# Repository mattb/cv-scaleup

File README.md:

# Control voltage step-up module

DC-coupled audio interfaces, such as the [MOTU 828 MkI](http://www.soundonsound.com/sos/jul01/articles/motu828.asp)
that I own, are capable
of [outputting voltages](http://www.expert-sleepers.co.uk/siwacompatibility.html) that can
control audio hardware such as
[Eurorack](http://electronicmusic.wikia.com/wiki/Eurorack) modules. However,
most Eurorack modules expect a CV range of -5v to 5v. I measured the MOTU as
outputting -2.88v to 2.88v.

This project contains Eagle files for a Eurorack-mountable opamp circuit with a gain that will
scale four MOTU outputs to the full CV range. It uses a single TL074 quad
op-amp and a few resistors. Calculations for the resistors were made using the calculator at 
http://earmark.net/gesr/opamp/gain_offset.htm

There is also a rudimentary 8HP front panel design in an Illustrator template.

On October 13th 2015, PCBs were ordered from OSHPark and panels from
Ponoko.  A single channel has been successfully tested on a
breadboard, and used to correctly track over 8 octaves of pitch control on
an Arturia Microbrute using Silent Way's Voice Controller plugin in Ableton Live.

On October 27th 2015, the PCBs arrived and the first one was assembled. All four channels worked correctly.

![Assembled board]
(assembled-board.jpg)

![Assembled panel]
(panel-assembled.jpg)

![Completed product in rack]
(panel-in-rack.jpg)

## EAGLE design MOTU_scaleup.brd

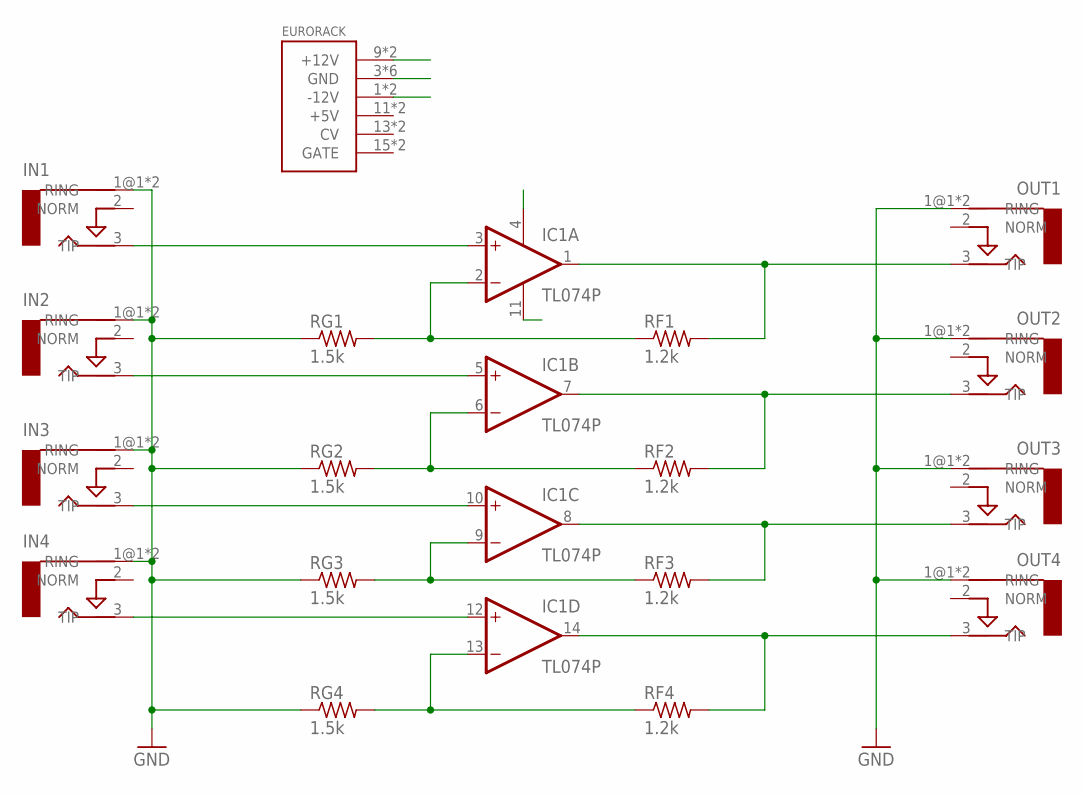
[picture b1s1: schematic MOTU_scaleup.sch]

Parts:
EURORACK: POWER; POWER_16
IC1: TL074P; DIL14
IN1, IN2, IN3, IN4: AUDIO-JACKERTHENVAR; ERTHENVAR-JACK
OUT1, OUT2, OUT3, OUT4: AUDIO-JACKERTHENVAR; ERTHENVAR-JACK
RF1, RF2, RF3, RF4: 1.2k; 0207/10
RG1, RG2, RG3, RG4: 1.5k; 0207/10

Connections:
+12V: EURORACK.9 (+12V), EURORACK.10 (+12V), IC1.4 (V+)
-12V: EURORACK.1 (-12V), EURORACK.2 (-12V), IC1.11 (V-)
GND: EURORACK.3 (GND), EURORACK.4 (GND), EURORACK.5 (GND), EURORACK.6 (GND), EURORACK.7 (GND), EURORACK.8 (GND), IN1.1@1 (RING), IN1.1@2 (RING), IN2.1@1 (RING), IN2.1@2 (RING), IN3.1@1 (RING), IN3.1@2 (RING), IN4.1@1 (RING), IN4.1@2 (RING), OUT1.1@1 (RING), OUT1.1@2 (RING), OUT2.1@1 (RING), OUT2.1@2 (RING), OUT3.1@1 (RING), OUT3.1@2 (RING), OUT4.1@1 (RING), OUT4.1@2 (RING), RG1.1, RG2.1, RG3.1, RG4.1
unnamed: IC1.3 (+IN), IN1.3 (TIP)
unnamed: IC1.5 (+IN), IN2.3 (TIP)
unnamed: IC1.10 (+IN), IN3.3 (TIP)
unnamed: IC1.12 (+IN), IN4.3 (TIP)
unnamed: IC1.14 (OUT), OUT4.3 (TIP), RF4.2
unnamed: IC1.8 (OUT), OUT3.3 (TIP), RF3.2
unnamed: IC1.7 (OUT), OUT2.3 (TIP), RF2.2
unnamed: IC1.1 (OUT), OUT1.3 (TIP), RF1.2
unnamed: IC1.6 (-IN), RF2.1, RG2.2
unnamed: IC1.9 (-IN), RF3.1, RG3.2
unnamed: IC1.13 (-IN), RF4.1, RG4.2
NNN: IC1.2 (-IN), RF1.1, RG1.2

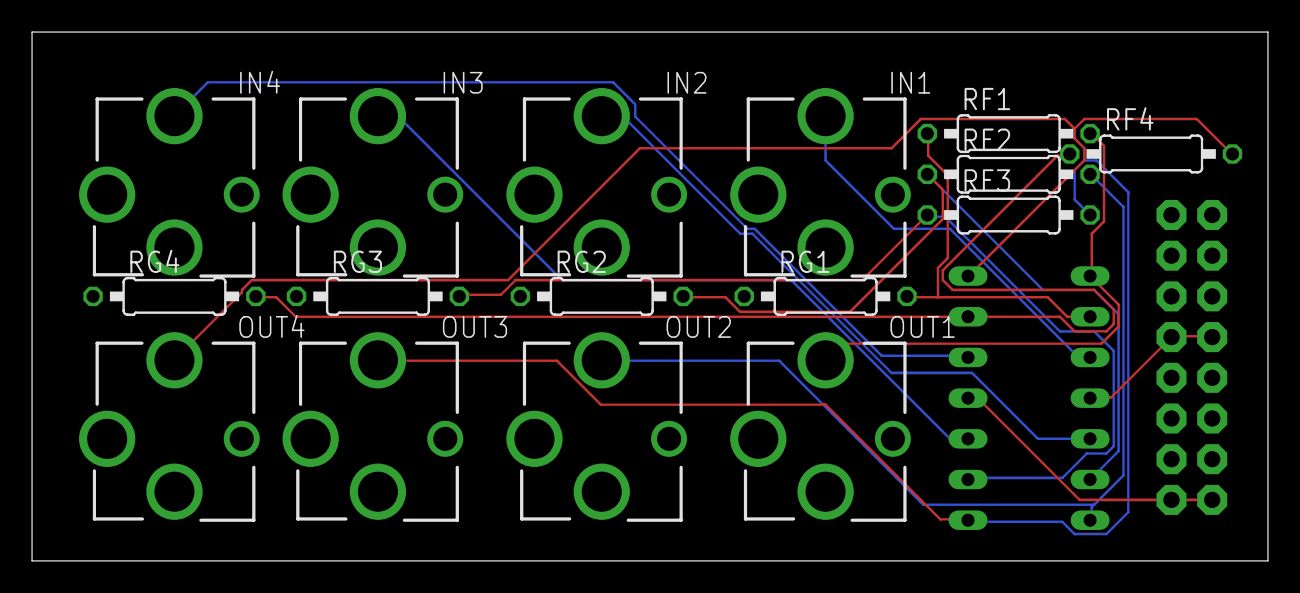
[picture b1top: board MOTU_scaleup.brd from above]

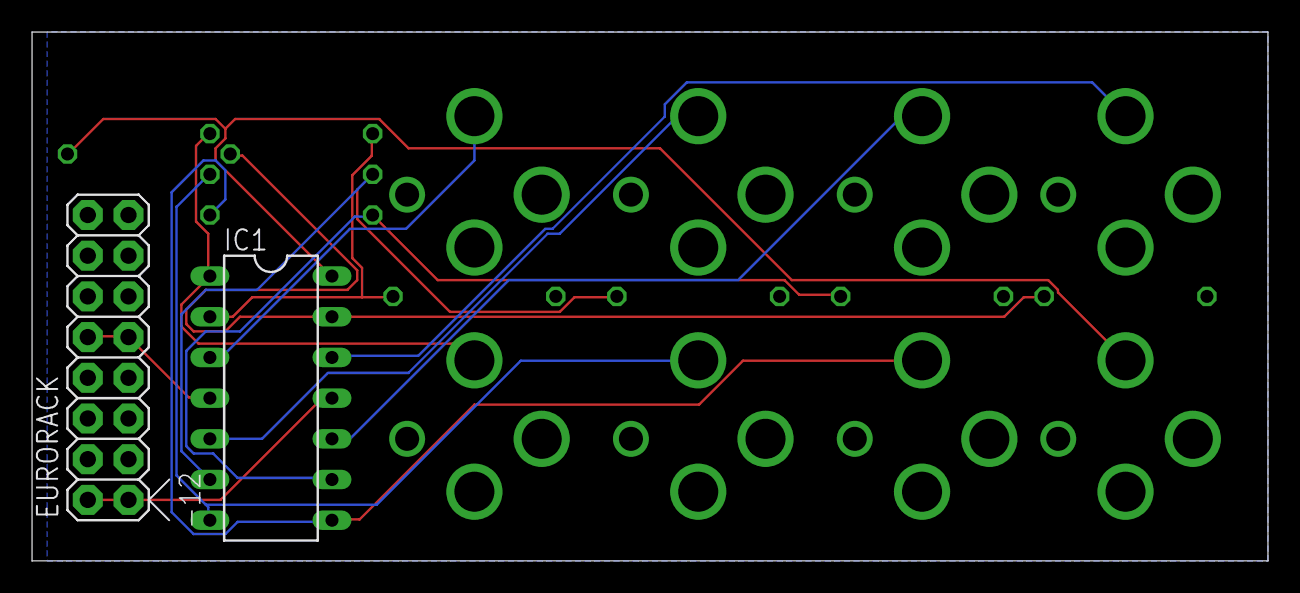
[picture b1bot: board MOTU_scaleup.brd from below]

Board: 2 copper layers, 77.1 x 33.0 mm, 18 parts (2 on the bottom side), 15 nets.

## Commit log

2015-10-14 init
2015-10-28 Assembly updates.
2015-11-01 Remade the panels after lots of errors at Ponoko for the first version.
2015-11-04 Final assembly pics
2015-11-04 Rotate pic
2015-11-04 Better rack source image.
